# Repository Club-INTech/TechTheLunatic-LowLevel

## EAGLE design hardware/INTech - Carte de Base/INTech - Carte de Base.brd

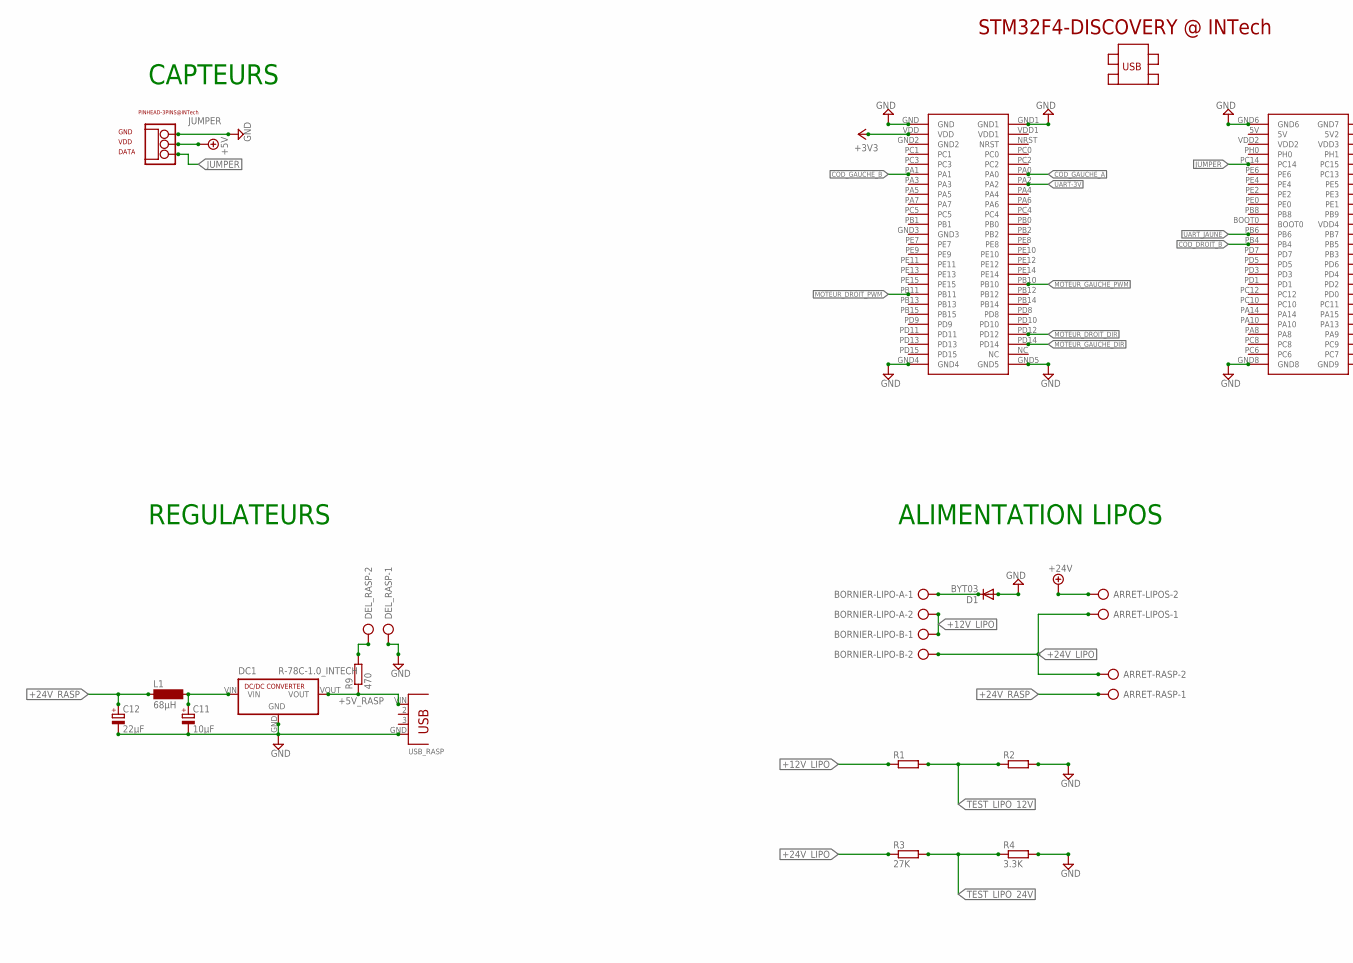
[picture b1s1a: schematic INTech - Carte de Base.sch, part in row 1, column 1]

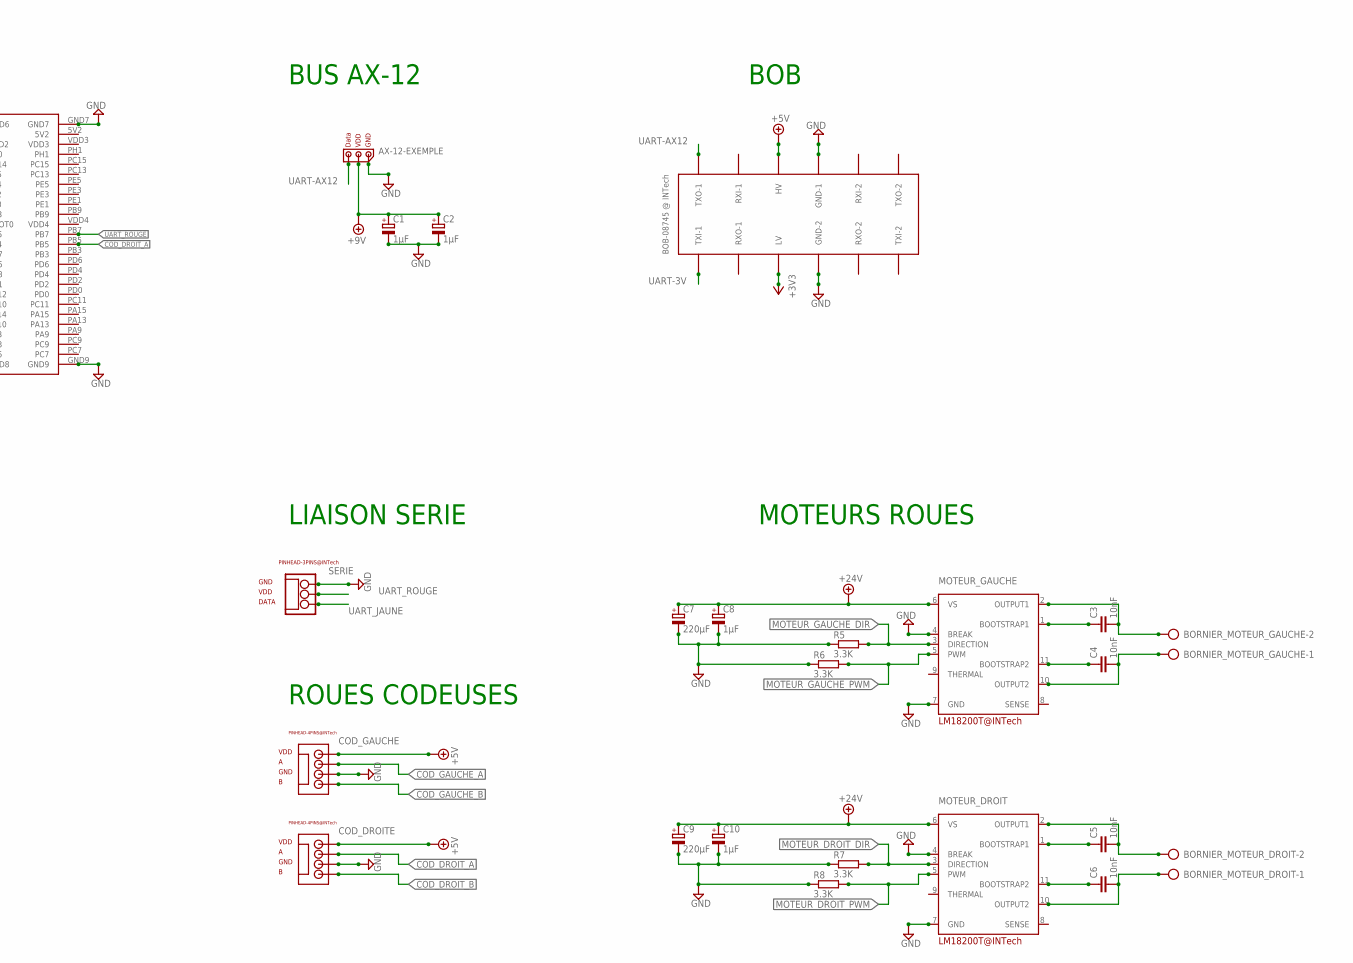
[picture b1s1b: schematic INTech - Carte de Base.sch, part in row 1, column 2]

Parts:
ARRET-LIPOS: AK300/2
ARRET-RASP: AK300/2
AX-12-EXEMPLE: AX-12_CF_INTECH
BORNIER-LIPO-A: AK300/2
BORNIER-LIPO-B: AK300/2
BORNIER_MOTEUR_DROIT: AK300/2
BORNIER_MOTEUR_GAUCHE: AK300/2
C1, C2: 1µF; E2,5-6E
C3, C4, C5, C6: 10nF; C050-025X075
C7, C9: 220µF; E3,5-8
C8, C10: 1µF; E3,5-8
C11: 10µF; E2,5-6
C12: 22µF; E2,5-6
COD_DROITE: PINHEAD-4_CF_INTECH
COD_GAUCHE: PINHEAD-4_CF_INTECH
D1: BYT03; DO27-15
DC1: R-78C-1.0_INTECH; SIP3_INTECH
DEL_RASP: AK300/2
JUMPER: PINHEAD_CF_INTECH
L1: 68µH; SD12K100
MOTEUR_DROIT: LM18200T_CF_INTECH
MOTEUR_GAUCHE: LM18200T_CF_INTECH
R1, R2: R-EU_0207/10; 0207/10
R3: 27K; 0207/10
R4, R5, R6, R7, R8: 3.3K; 0207/10
R9: 470; 0204/7
SERIE: PINHEAD_CF_INTECH
U$1: STM32F4-DISCOVERY
U$2: BOB-08745
USB_RASP: USB_87520; USB

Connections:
+3V3: U$1.VDD, U$2.LV
+5V: COD_DROITE.VDD, COD_GAUCHE.VDD, JUMPER.VDD, U$2.HV
+5V_RASP: DC1.VOUT, R9.1, USB_RASP.VIN
+9V: AX-12-EXEMPLE.VDD, C1.+, C2.+
+12V_LIPO: BORNIER-LIPO-A.2, BORNIER-LIPO-B.1, R1.1
+24V: ARRET-LIPOS.2, C7.+, C8.+, C9.+, C10.+, MOTEUR_DROIT.6 (VS), MOTEUR_GAUCHE.6 (VS)
+24V_LIPO: ARRET-LIPOS.1, ARRET-RASP.2, BORNIER-LIPO-B.2, R3.1
+24V_RASP: ARRET-RASP.1, C12.+, L1.1
COD_DROIT_A: COD_DROITE.A, U$1.PB5
COD_DROIT_B: COD_DROITE.B, U$1.PB4
COD_GAUCHE_A: COD_GAUCHE.A, U$1.PA0
COD_GAUCHE_B: COD_GAUCHE.B, U$1.PA1
GND: AX-12-EXEMPLE.GND, C1.-, C2.-, C7.-, C8.-, C9.-, C10.-, C11.-, C12.-, COD_DROITE.GND, COD_GAUCHE.GND, D1.A, DC1.GND, DEL_RASP.1, JUMPER.GND, MOTEUR_DROIT.4 (BREAK), MOTEUR_DROIT.7 (GND), MOTEUR_GAUCHE.4 (BREAK), MOTEUR_GAUCHE.7 (GND), R2.2, R4.2, R5.1, R6.1, R7.1, R8.1, SERIE.GND, U$1.GND, U$1.GND1, U$1.GND4, U$1.GND5, U$1.GND6, U$1.GND7, U$1.GND8, U$1.GND9, U$2.GND-1, U$2.GND-2, USB_RASP.GND
JUMPER: JUMPER.DATA, U$1.PC14
MOTEUR_DROIT_DIR: MOTEUR_DROIT.3 (DIRECTION), R7.2, U$1.PD12
MOTEUR_DROIT_PWM: MOTEUR_DROIT.5 (PWM), R8.2, U$1.PB11
MOTEUR_GAUCHE_DIR: MOTEUR_GAUCHE.3 (DIRECTION), R5.2, U$1.PD14
MOTEUR_GAUCHE_PWM: MOTEUR_GAUCHE.5 (PWM), R6.2, U$1.PB10
unnamed: BORNIER-LIPO-A.1, D1.C
unnamed: C4.1, MOTEUR_GAUCHE.11 (BOOTSTRAP2)
unnamed: C3.1, MOTEUR_GAUCHE.1 (BOOTSTRAP1)
unnamed: C5.1, MOTEUR_DROIT.1 (BOOTSTRAP1)
unnamed: C6.1, MOTEUR_DROIT.11 (BOOTSTRAP2)
unnamed: C11.+, DC1.VIN, L1.2
unnamed: DEL_RASP.2, R9.2
unnamed: BORNIER_MOTEUR_GAUCHE.2, C3.2, MOTEUR_GAUCHE.2 (OUTPUT1)
unnamed: BORNIER_MOTEUR_GAUCHE.1, C4.2, MOTEUR_GAUCHE.10 (OUTPUT2)
unnamed: BORNIER_MOTEUR_DROIT.2, C5.2, MOTEUR_DROIT.2 (OUTPUT1)
unnamed: BORNIER_MOTEUR_DROIT.1, C6.2, MOTEUR_DROIT.10 (OUTPUT2)
TEST_LIPO_12V: R1.2, R2.1
TEST_LIPO_24V: R3.2, R4.1
UART-3V: U$1.PA2, U$2.TXI-1
UART-AX12: AX-12-EXEMPLE.DATA, U$2.TXO-1
UART_JAUNE: SERIE.DATA, U$1.PB6
UART_ROUGE: SERIE.VDD, U$1.PB7

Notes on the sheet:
BUS AX-12
BOB
ALIMENTATION LIPOS
LIAISON SERIE
MOTEURS ROUES
ROUES CODEUSES
CAPTEURS
REGULATEURS

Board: 2 copper layers, 41 parts (0 on the bottom side), 35 nets, no tracks yet.

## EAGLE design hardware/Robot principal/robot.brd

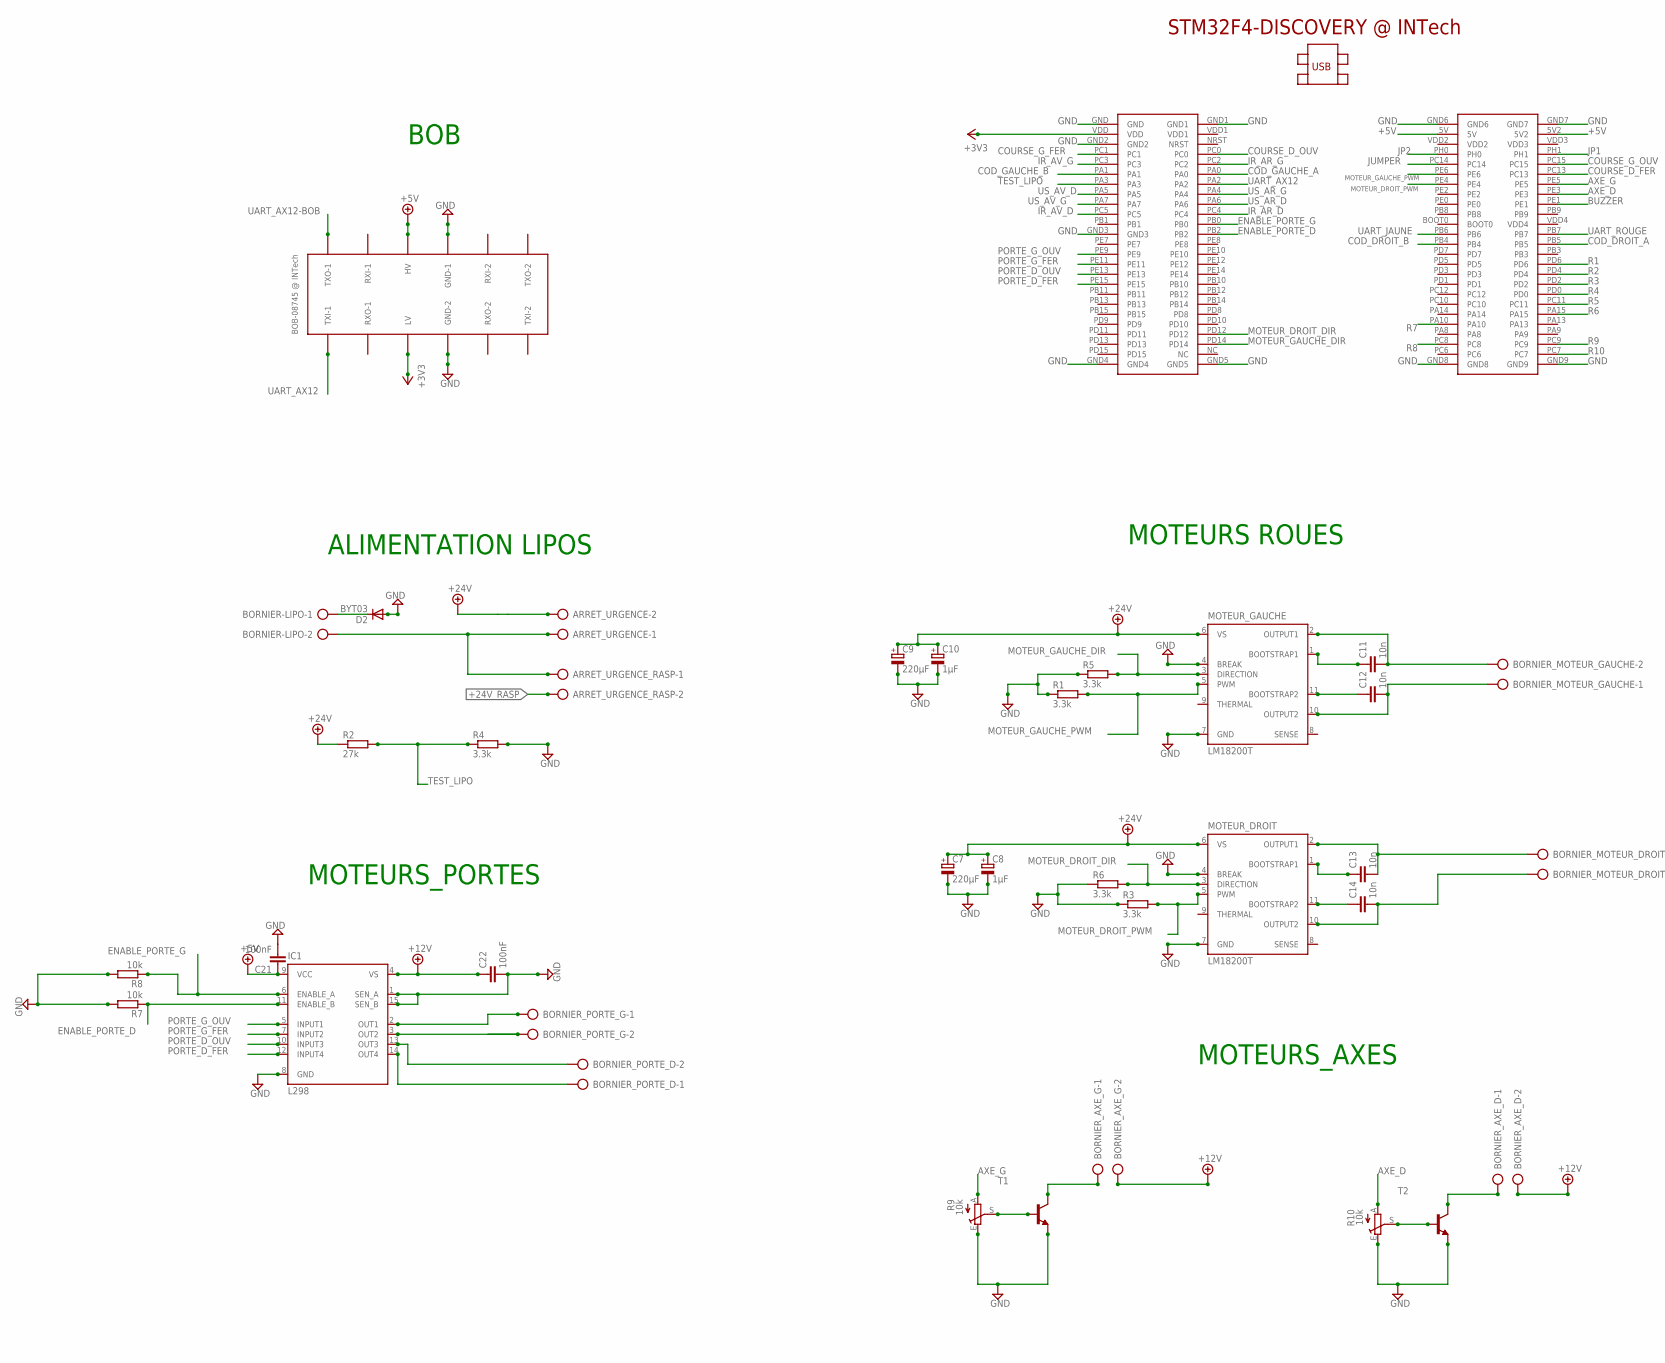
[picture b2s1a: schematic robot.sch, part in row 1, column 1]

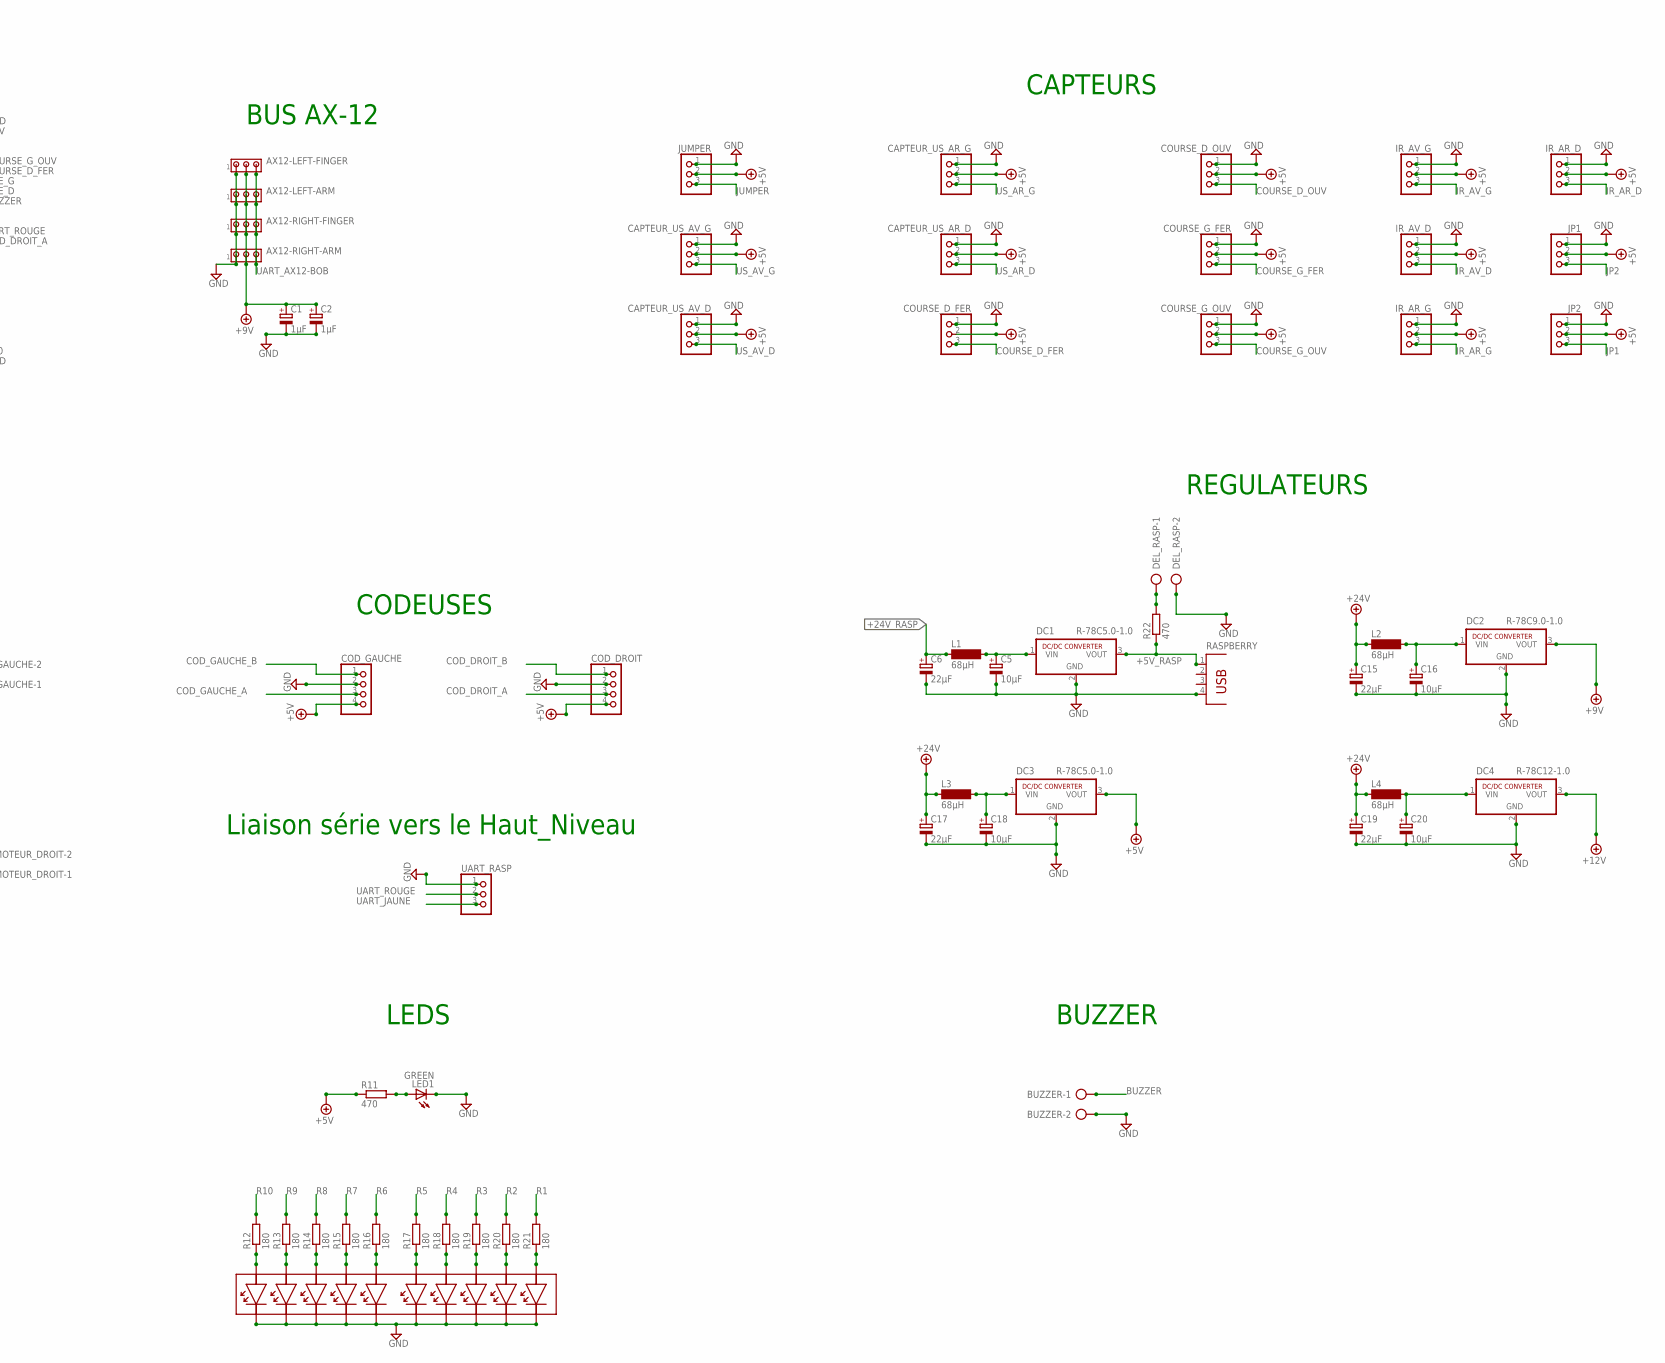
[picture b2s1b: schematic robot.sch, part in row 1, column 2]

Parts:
ARRET_URGENCE: AK300/2
ARRET_URGENCE_RASP: AK300/2
AX12-LEFT-ARM, AX12-LEFT-FINGER, AX12-RIGHT-ARM, AX12-RIGHT-FINGER: MTA03-100; 10X03MTA
BOB-08745: BOB-08745
BORNIER-LIPO: AK300/2
BORNIER_AXE_D: AK300/2
BORNIER_AXE_G: AK300/2
BORNIER_MOTEUR_DROIT: AK300/2
BORNIER_MOTEUR_GAUCHE: AK300/2
BORNIER_PORTE_D: AK300/2
BORNIER_PORTE_G: AK300/2
BUZZER: AK300/2
C1, C2: 1µF; E2,5-6E
C5, C16, C18, C20: 10µF; E2,5-6E
C6, C15, C17, C19: 22µF; E2,5-6E
C7, C9: 220µF; E3,5-8
C8, C10: 1µF; E3,5-8
C11, C12, C13, C14: 10n; C050-025X075
C21, C22: 100nF; C050-024X044
CAPTEUR_US_AR_D: PINHD-1X3; 1X03
CAPTEUR_US_AR_G: PINHD-1X3; 1X03
CAPTEUR_US_AV_D: PINHD-1X3; 1X03
CAPTEUR_US_AV_G: PINHD-1X3; 1X03
COD_DROIT: PINHD-1X4; 1X04
COD_GAUCHE: PINHD-1X4; 1X04
COURSE_D_FER: PINHD-1X3; 1X03
COURSE_D_OUV: PINHD-1X3; 1X03
COURSE_G_FER: PINHD-1X3; 1X03
COURSE_G_OUV: PINHD-1X3; 1X03
D2: BYT03; DO27-15
DC1, DC3: R-78C5.0-1.0; SIP3
DC2: R-78C9.0-1.0; SIP3
DC4: R-78C12-1.0; SIP3
DEL_RASP: AK300/2
IC1: L298; MULTIWATT-15
IR_AR_D: PINHD-1X3; 1X03
IR_AR_G: PINHD-1X3; 1X03
IR_AV_D: PINHD-1X3; 1X03
IR_AV_G: PINHD-1X3; 1X03
JP1, JP2: PINHD-1X3; 1X03
JUMPER: PINHD-1X3; 1X03
L1, L2, L3, L4: 68µH; SD12K100
LED1: GREEN; LED5MM
MOTEUR_DROIT: LM18200T; TO-220-11
MOTEUR_GAUCHE: LM18200T; TO-220-11
R1, R3: 3.3k; 0207/7
R2: 27k; 0207/10
R4, R5, R6: 3.3k; 0207/10
R7, R8: 10k; 0207/10
R9, R10: 10k; CA9H
R11: 470; 0207/2V
R12, R13, R14, R15, R16, R17, R18, R19, R20, R21: 180; 0207/2V
R22: 470; 0204/7
RASPBERRY: PN87520
T1, T2: 2N5400-NPN-TO92-CBE; TO92-CBE
U$1: STM32F4-DISCOVERY
U$2: DELS10RACK
UART_RASP: PINHD-1X3; 1X03

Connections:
+3V3: BOB-08745.LV, U$1.VDD
+5V: BOB-08745.HV, C21.1, CAPTEUR_US_AR_D.2, CAPTEUR_US_AR_G.2, CAPTEUR_US_AV_D.2, CAPTEUR_US_AV_G.2, COD_DROIT.4, COD_GAUCHE.4, COURSE_D_FER.2, COURSE_D_OUV.2, COURSE_G_FER.2, COURSE_G_OUV.2, DC3.3 (VOUT), IC1.9 (VCC), IR_AR_D.2, IR_AR_G.2, IR_AV_D.2, IR_AV_G.2, JP1.2, JP2.2, JUMPER.2, R11.1, U$1.5V, U$1.5V2
+5V_RASP: DC1.3 (VOUT), R22.1, RASPBERRY.1
+9V: AX12-LEFT-ARM.2, AX12-LEFT-FINGER.2, AX12-RIGHT-ARM.2, AX12-RIGHT-FINGER.2, C1.+, C2.+, DC2.3 (VOUT)
+12V: BORNIER_AXE_D.2, BORNIER_AXE_G.2, C22.1, DC4.3 (VOUT), IC1.4 (VS)
+24V: ARRET_URGENCE.2, C7.+, C8.+, C9.+, C10.+, C15.+, C17.+, C19.+, L2.1, L3.1, L4.1, MOTEUR_DROIT.6 (VS), MOTEUR_GAUCHE.6 (VS), R2.1
+24V_LIPO: ARRET_URGENCE.1, ARRET_URGENCE_RASP.1, BORNIER-LIPO.2
+24V_RASP: ARRET_URGENCE_RASP.2, C6.+, L1.1
AXE_D: R10.A, U$1.PE3
AXE_G: R9.A, U$1.PE5
BUZZER: BUZZER.1, U$1.PE1
COD_DROIT_A: COD_DROIT.3, U$1.PB5
COD_DROIT_B: COD_DROIT.1, U$1.PB4
COD_GAUCHE_A: COD_GAUCHE.3, U$1.PA0
COD_GAUCHE_B: COD_GAUCHE.1, U$1.PA1
COURSE_D_FER: COURSE_D_FER.3, U$1.PC13
COURSE_D_OUV: COURSE_D_OUV.3, U$1.PC0
COURSE_G_FER: COURSE_G_FER.3, U$1.PC1
COURSE_G_OUV: COURSE_G_OUV.3, U$1.PC15
ENABLE_PORTE_D: IC1.11 (ENABLE_B), R7.1, U$1.PB2
ENABLE_PORTE_G: IC1.6 (ENABLE_A), R8.1, U$1.PB0
GND: AX12-LEFT-ARM.1, AX12-LEFT-FINGER.1, AX12-RIGHT-ARM.1, AX12-RIGHT-FINGER.1, BOB-08745.GND-1, BOB-08745.GND-2, BUZZER.2, C1.-, C2.-, C5.-, C6.-, C7.-, C8.-, C9.-, C10.-, C15.-, C16.-, C17.-, C18.-, C19.-, C20.-, C21.2, C22.2, CAPTEUR_US_AR_D.1, CAPTEUR_US_AR_G.1, CAPTEUR_US_AV_D.1, CAPTEUR_US_AV_G.1, COD_DROIT.2, COD_GAUCHE.2, COURSE_D_FER.1, COURSE_D_OUV.1, COURSE_G_FER.1, COURSE_G_OUV.1, D2.A, DC1.2 (GND), DC2.2 (GND), DC3.2 (GND), DC4.2 (GND), DEL_RASP.2, IC1.1 (SEN_A), IC1.8 (GND), IC1.15 (SEN_B), IR_AR_D.1, IR_AR_G.1, IR_AV_D.1, IR_AV_G.1, JP1.1, JP2.1, JUMPER.1, LED1.K (C), MOTEUR_DROIT.4 (BREAK), MOTEUR_DROIT.7 (GND), MOTEUR_GAUCHE.4 (BREAK), MOTEUR_GAUCHE.7 (GND), R1.1, R3.1, R4.2, R5.1, R6.1, R7.2, R8.2, R9.E, R10.E, RASPBERRY.4, T1.E, T2.E, U$1.GND, U$1.GND1, U$1.GND2, U$1.GND3, U$1.GND4, U$1.GND5, U$1.GND6, U$1.GND7, U$1.GND8, U$1.GND9, U$2.11, U$2.12, U$2.13, U$2.14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
IR_AR_D: IR_AR_D.3, U$1.PC4
IR_AR_G: IR_AR_G.3, U$1.PC2
IR_AV_D: IR_AV_D.3, U$1.PC5
IR_AV_G: IR_AV_G.3, U$1.PC3
JP1: JP2.3, U$1.PH1
JP2: JP1.3, U$1.PH0
JUMPER: JUMPER.3, U$1.PC14
MOTEUR_DROIT_DIR: MOTEUR_DROIT.3 (DIRECTION), R6.2, U$1.PD12
MOTEUR_DROIT_PWM: MOTEUR_DROIT.5 (PWM), R3.2, U$1.PE4
MOTEUR_GAUCHE_DIR: MOTEUR_GAUCHE.3 (DIRECTION), R5.2, U$1.PD14
MOTEUR_GAUCHE_PWM: MOTEUR_GAUCHE.5 (PWM), R1.2, U$1.PE6
unnamed: R10.S, T2.B
unnamed: R9.S, T1.B
unnamed: DEL_RASP.1, R22.2
unnamed: BORNIER-LIPO.1, D2.C
unnamed: BORNIER_AXE_G.1, T1.C
unnamed: LED1.A, R11.2
unnamed: BORNIER_PORTE_D.1, IC1.14 (OUT4)
unnamed: C14.1, MOTEUR_DROIT.11 (BOOTSTRAP2)
unnamed: BORNIER_MOTEUR_GAUCHE.1, C12.2, MOTEUR_GAUCHE.10 (OUTPUT2)
unnamed: C11.1, MOTEUR_GAUCHE.1 (BOOTSTRAP1)
unnamed: BORNIER_MOTEUR_DROIT.2, C13.2, MOTEUR_DROIT.2 (OUTPUT1)
unnamed: BORNIER_MOTEUR_DROIT.1, C14.2, MOTEUR_DROIT.10 (OUTPUT2)
unnamed: C20.+, DC4.1 (VIN), L4.2
unnamed: C13.1, MOTEUR_DROIT.1 (BOOTSTRAP1)
unnamed: C5.+, DC1.1 (VIN), L1.2
unnamed: BORNIER_MOTEUR_GAUCHE.2, C11.2, MOTEUR_GAUCHE.2 (OUTPUT1)
unnamed: C18.+, DC3.1 (VIN), L3.2
unnamed: C12.1, MOTEUR_GAUCHE.11 (BOOTSTRAP2)
unnamed: C16.+, DC2.1 (VIN), L2.2
unnamed: R12.1, U$2.10
unnamed: R13.1, U$2.9
unnamed: BORNIER_AXE_D.1, T2.C
unnamed: R14.1, U$2.8
unnamed: BORNIER_PORTE_G.1, IC1.2 (OUT1)
unnamed: R15.1, U$2.7
unnamed: BORNIER_PORTE_G.2, IC1.3 (OUT2)
unnamed: BORNIER_PORTE_D.2, IC1.13 (OUT3)
unnamed: R16.1, U$2.6
unnamed: R17.1, U$2.5
unnamed: R18.1, U$2.4
unnamed: R19.1, U$2.3
unnamed: R20.1, U$2.2
unnamed: R21.1, U$2.1
PORTE_D_FER: IC1.12 (INPUT4), U$1.PE15
PORTE_D_OUV: IC1.10 (INPUT3), U$1.PE13
PORTE_G_FER: IC1.7 (INPUT2), U$1.PE11
PORTE_G_OUV: IC1.5 (INPUT1), U$1.PE9
R1: R21.2, U$1.PD6
R2: R20.2, U$1.PD4
R3: R19.2, U$1.PD2
R4: R18.2, U$1.PD0
R5: R17.2, U$1.PC11
R6: R16.2, U$1.PA15
R7: R15.2, U$1.PA10
R8: R14.2, U$1.PC8
R9: R13.2, U$1.PC9
R10: R12.2, U$1.PC7
TEST_LIPO: R2.2, R4.1, U$1.PA3
UART_AX12: BOB-08745.TXI-1, U$1.PA2
UART_AX12-BOB: AX12-LEFT-ARM.3, AX12-LEFT-FINGER.3, AX12-RIGHT-ARM.3, AX12-RIGHT-FINGER.3, BOB-08745.TXO-1
UART_JAUNE: U$1.PB6, UART_RASP.3
UART_ROUGE: U$1.PB7, UART_RASP.2
US_AR_D: CAPTEUR_US_AR_D.3, U$1.PA6
US_AR_G: CAPTEUR_US_AR_G.3, U$1.PA4
US_AV_D: CAPTEUR_US_AV_D.3, U$1.PA5
US_AV_G: CAPTEUR_US_AV_G.3, U$1.PA7

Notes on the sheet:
BUS AX-12
CAPTEURS
CODEUSES
Liaison série vers le Haut_Niveau
MOTEURS ROUES
REGULATEURS
BOB
ALIMENTATION LIPOS
MOTEURS_PORTES
MOTEURS_AXES
LEDS
BUZZER

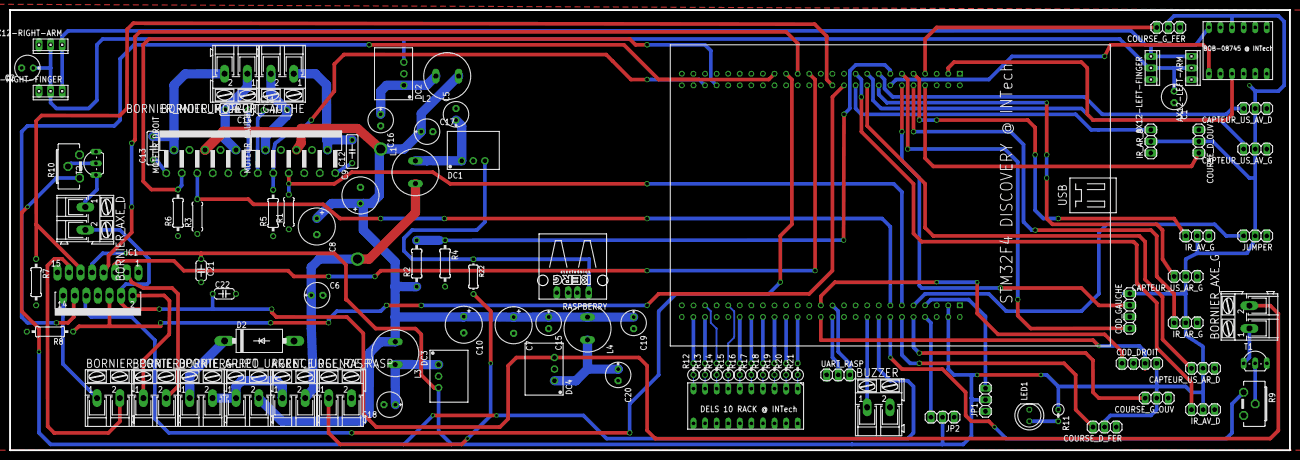
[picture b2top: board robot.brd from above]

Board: 2 copper layers, 280.7 x 96.5 mm, 94 parts (0 on the bottom side), 89 nets.

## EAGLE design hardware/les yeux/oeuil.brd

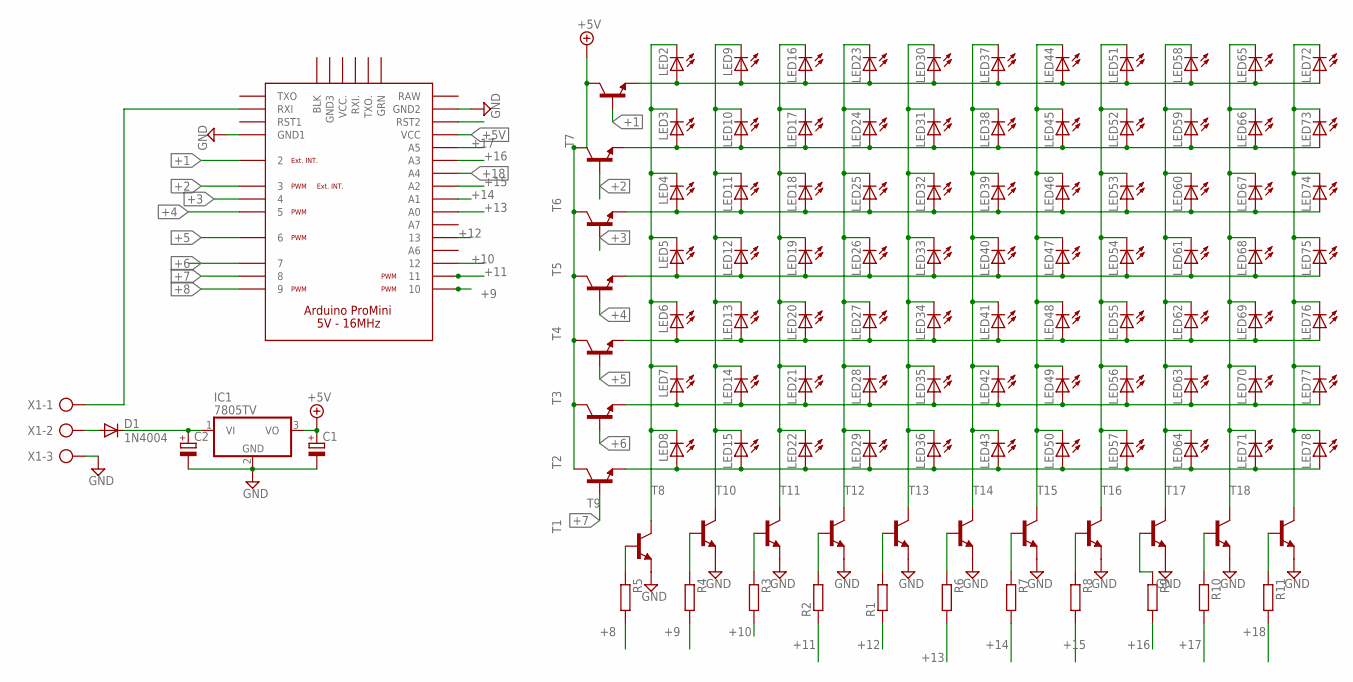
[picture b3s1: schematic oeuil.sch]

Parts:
C1, C2: CPOL-EUE2,5-6E; E2,5-6E
D1: 1N4004; DO41-10
IC1: 7805TV; TO220V
LED2, LED3, LED4, LED5, LED6, LED7, LED8, LED9, LED10, LED11, LED12, LED13, LED14, LED15, LED16, LED17, LED18, LED19, LED20, LED21, LED22, LED23, LED24, LED25, LED26, LED27, LED28, LED29, LED30, LED31, LED32, LED33, LED34, LED35, LED36, LED37, LED38, LED39, LED40, LED41, LED42, LED43, LED44, LED45, LED46, LED47, LED48, LED49, LED50, LED51, LED52, LED53, LED54, LED55, LED56, LED57, LED58, LED59, LED60, LED61, LED62, LED63, LED64, LED65, LED66, LED67, LED68, LED69, LED70, LED71, LED72, LED73, LED74, LED75, LED76, LED77, LED78: LED3MM
R1, R2, R3, R4, R5, R6, R7, R8, R9, R10, R11: R-EU_0207/2V; 0207/2V
T1, T2, T3, T4, T5, T6, T7, T8, T9, T10, T11, T12, T13, T14, T15, T16, T17, T18: 2N4124-NPN-TO92-CBE; TO92-CBE
U$1: ARDUINO_PRO_MINI
X1: AK300/3

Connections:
+1: T7.B, U$1.2
+2: T6.B, U$1.3
+3: T5.B, U$1.4
+4: T4.B, U$1.5
+5: T3.B, U$1.6
+5V: C1.+, IC1.3 (VO), T1.C, T2.C, T3.C, T4.C, T5.C, T6.C, T7.C, U$1.VCC1 (VCC)
+6: T2.B, U$1.7
+7: T1.B, U$1.8
+8: R5.2, U$1.9
+9: R4.2, U$1.10
+10: R3.2, U$1.12
+11: R2.1, U$1.11
+12: R1.1, U$1.13
+13: R6.2, U$1.A0
+14: R7.2, U$1.A1
+15: R8.2, U$1.A2
+16: R9.2, U$1.A3
+17: R10.2, U$1.A5
+18: R11.2, U$1.A4
GND: C1.-, C2.-, IC1.2 (GND), T8.E, T9.E, T10.E, T11.E, T12.E, T13.E, T14.E, T15.E, T16.E, T17.E, T18.E, U$1.GND1, U$1.GND2, X1.3
unnamed: C2.+, D1.C, IC1.1 (VI)
unnamed: LED9.K (C), LED10.K (C), LED11.K (C), LED12.K (C), LED13.K (C), LED14.K (C), LED15.K (C), T8.C
unnamed: LED16.K (C), LED17.K (C), LED18.K (C), LED19.K (C), LED20.K (C), LED21.K (C), LED22.K (C), T10.C
unnamed: LED51.K (C), LED52.K (C), LED53.K (C), LED54.K (C), LED55.K (C), LED56.K (C), LED57.K (C), T15.C
unnamed: LED23.K (C), LED24.K (C), LED25.K (C), LED26.K (C), LED27.K (C), LED28.K (C), LED29.K (C), T11.C
unnamed: LED30.K (C), LED31.K (C), LED32.K (C), LED33.K (C), LED34.K (C), LED35.K (C), LED36.K (C), T12.C
unnamed: LED37.K (C), LED38.K (C), LED39.K (C), LED40.K (C), LED41.K (C), LED42.K (C), LED43.K (C), T13.C
unnamed: LED44.K (C), LED45.K (C), LED46.K (C), LED47.K (C), LED48.K (C), LED49.K (C), LED50.K (C), T14.C
unnamed: LED58.K (C), LED59.K (C), LED60.K (C), LED61.K (C), LED62.K (C), LED63.K (C), LED64.K (C), T16.C
unnamed: LED65.K (C), LED66.K (C), LED67.K (C), LED68.K (C), LED69.K (C), LED70.K (C), LED71.K (C), T17.C
unnamed: LED72.K (C), LED73.K (C), LED74.K (C), LED75.K (C), LED76.K (C), LED77.K (C), LED78.K (C), T18.C
unnamed: LED8.A, LED15.A, LED22.A, LED29.A, LED36.A, LED43.A, LED50.A, LED57.A, LED64.A, LED71.A, LED78.A, T1.E
unnamed: R5.1, T9.B
unnamed: R4.1, T8.B
unnamed: R3.1, T10.B
unnamed: R2.2, T11.B
unnamed: R1.2, T12.B
unnamed: R6.1, T13.B
unnamed: R7.1, T14.B
unnamed: R8.1, T15.B
unnamed: R9.1, T16.B
unnamed: R10.1, T17.B
unnamed: R11.1, T18.B
unnamed: LED2.A, LED9.A, LED16.A, LED23.A, LED30.A, LED37.A, LED44.A, LED51.A, LED58.A, LED65.A, LED72.A, T7.E
unnamed: D1.A, X1.2
unnamed: U$1.RXI1 (RXI), X1.1
unnamed: LED6.A, LED13.A, LED20.A, LED27.A, LED34.A, LED41.A, LED48.A, LED55.A, LED62.A, LED69.A, LED76.A, T3.E
unnamed: LED7.A, LED14.A, LED21.A, LED28.A, LED35.A, LED42.A, LED49.A, LED56.A, LED63.A, LED70.A, LED77.A, T2.E
unnamed: LED5.A, LED12.A, LED19.A, LED26.A, LED33.A, LED40.A, LED47.A, LED54.A, LED61.A, LED68.A, LED75.A, T4.E
unnamed: LED4.A, LED11.A, LED18.A, LED25.A, LED32.A, LED39.A, LED46.A, LED53.A, LED60.A, LED67.A, LED74.A, T5.E
unnamed: LED3.A, LED10.A, LED17.A, LED24.A, LED31.A, LED38.A, LED45.A, LED52.A, LED59.A, LED66.A, LED73.A, T6.E
unnamed: LED2.K (C), LED3.K (C), LED4.K (C), LED5.K (C), LED6.K (C), LED7.K (C), LED8.K (C), T9.C

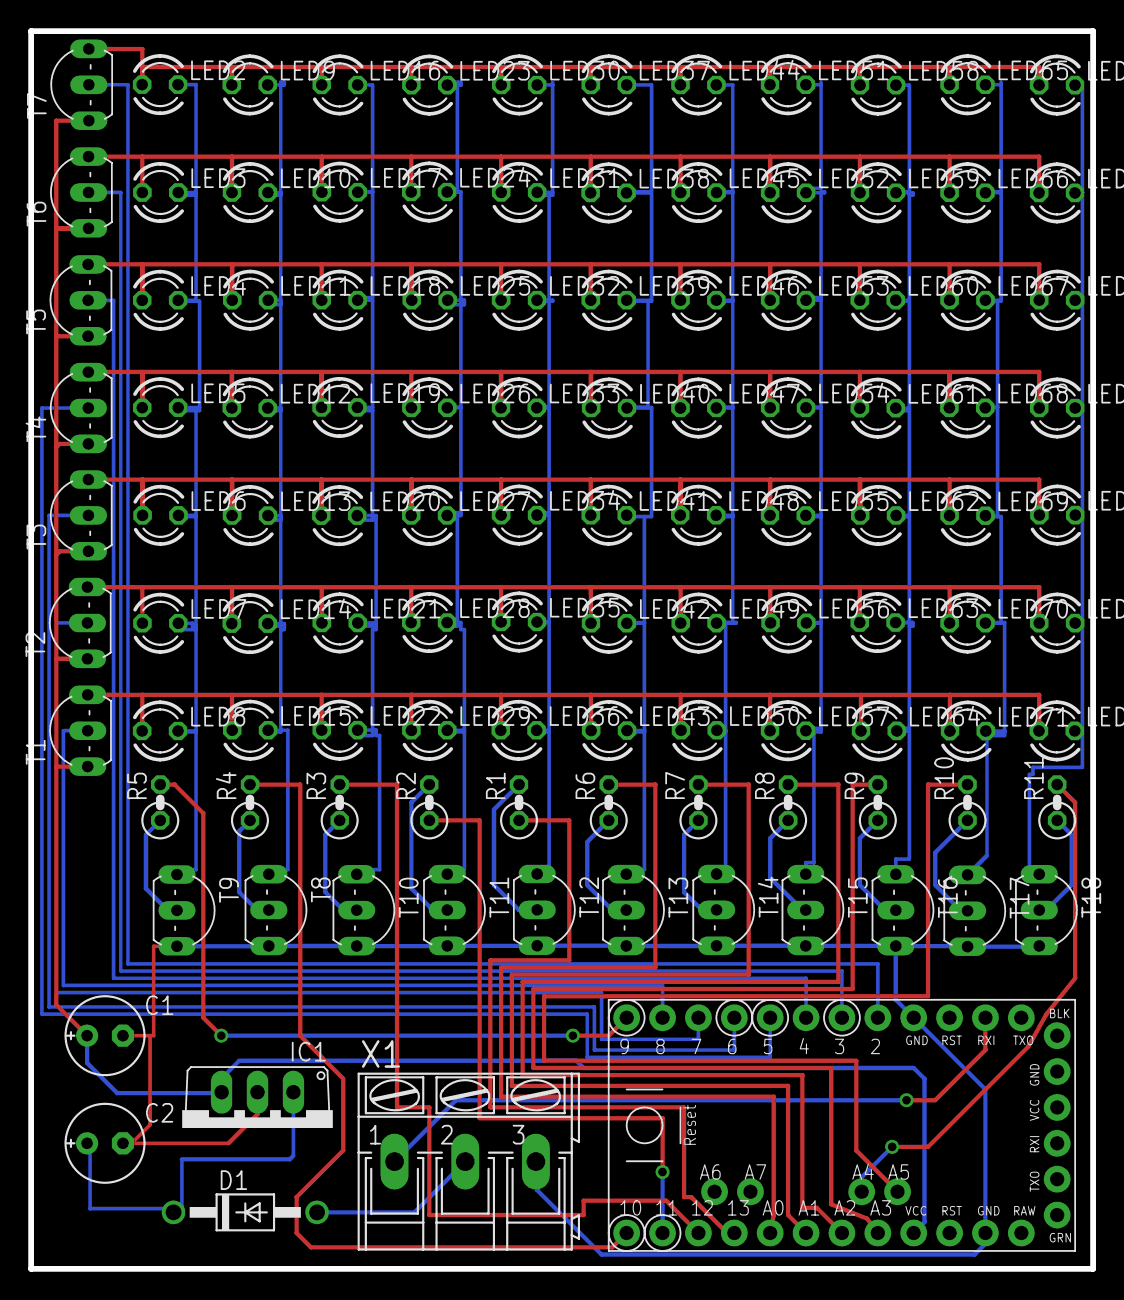
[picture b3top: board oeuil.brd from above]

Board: 2 copper layers, 75.2 x 87.6 mm, 112 parts (0 on the bottom side), 52 nets.

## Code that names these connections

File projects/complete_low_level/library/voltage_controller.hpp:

#include "stm32f4xx.h"
#include "safe_enum.hpp"
#include "utils.h"
#include "stm32f4xx_gpio.h"
#include "stm32f4xx_tim.h"
#include "stm32f4xx_rcc.h"
#include "stm32f4xx_adc.h"

/**
 * Permet de mesurer la tension de la LiPO et l'affiche sur un indicateur � 10 LEDs
 *
 * LEDS:
 * 1: PC7
 * 2: PC8
 * 3: PC9
 * 4: PE0
 * 5: PA15
 * 6: PC11
 * 7: PD0
 * 8: PD2
 * 9: PD4
 * 10: PD6
 * @author discord & sa maman
 */
class Voltage_controller : public Singleton<Voltage_controller>
{
public:
	Voltage_controller()
	{
		counter = 0;
		blink = false;
		minimal_voltage = 4086;
		usb_voltage = 600;
		voltage_echelon = 80;

		RCC_AHB1PeriphClockCmd(RCC_AHB1Periph_GPIOB, ENABLE);
		RCC_AHB1PeriphClockCmd(RCC_AHB1Periph_GPIOD, ENABLE);
		RCC_AHB1PeriphClockCmd(RCC_AHB1Periph_GPIOC, ENABLE);
		RCC_AHB1PeriphClockCmd(RCC_AHB1Periph_GPIOA, ENABLE);
		RCC_AHB1PeriphClockCmd(RCC_AHB1Periph_GPIOE, ENABLE);

		GPIO_InitTypeDef GPIO_InitStruct;
		GPIO_StructInit(&GPIO_InitStruct); //Remplit avec les valeurs par d�faut

		GPIO_InitStruct.GPIO_Pin = GPIO_Pin_6;
		GPIO_InitStruct.GPIO_Mode = GPIO_Mode_OUT;
		GPIO_InitStruct.GPIO_Speed = GPIO_Speed_100MHz;
		GPIO_Init(GPIOD, &GPIO_InitStruct);

		GPIO_StructInit(&GPIO_InitStruct); //Remplit avec les valeurs par d�faut

		GPIO_InitStruct.GPIO_Pin = GPIO_Pin_4;
		GPIO_InitStruct.GPIO_Mode = GPIO_Mode_OUT;
		GPIO_InitStruct.GPIO_Speed = GPIO_Speed_100MHz;
		GPIO_Init(GPIOD, &GPIO_InitStruct);

		GPIO_StructInit(&GPIO_InitStruct); //Remplit avec les valeurs par d�faut

		GPIO_InitStruct.GPIO_Pin = GPIO_Pin_2;
		GPIO_InitStruct.GPIO_Mode = GPIO_Mode_OUT;
		GPIO_InitStruct.GPIO_Speed = GPIO_Speed_100MHz;
		GPIO_Init(GPIOD, &GPIO_InitStruct);

		GPIO_StructInit(&GPIO_InitStruct); //Remplit avec les valeurs par d�faut

		GPIO_InitStruct.GPIO_Pin = GPIO_Pin_0;
		GPIO_InitStruct.GPIO_Mode = GPIO_Mode_OUT;
		GPIO_InitStruct.GPIO_Speed = GPIO_Speed_100MHz;
		GPIO_Init(GPIOD, &GPIO_InitStruct);

		GPIO_StructInit(&GPIO_InitStruct); //Remplit avec les valeurs par d�faut

		GPIO_InitStruct.GPIO_Pin = GPIO_Pin_11;
		GPIO_InitStruct.GPIO_Mode = GPIO_Mode_OUT;
		GPIO_InitStruct.GPIO_Speed = GPIO_Speed_100MHz;
		GPIO_Init(GPIOC, &GPIO_InitStruct);

		GPIO_StructInit(&GPIO_InitStruct); //Remplit avec les valeurs par d�faut

		GPIO_InitStruct.GPIO_Pin = GPIO_Pin_15;
		GPIO_InitStruct.GPIO_Mode = GPIO_Mode_OUT;
		GPIO_InitStruct.GPIO_Speed = GPIO_Speed_100MHz;
		GPIO_Init(GPIOA, &GPIO_InitStruct);

		GPIO_StructInit(&GPIO_InitStruct); //Remplit avec les valeurs par d�faut

		GPIO_InitStruct.GPIO_Pin = GPIO_Pin_0;
		GPIO_InitStruct.GPIO_Mode = GPIO_Mode_OUT;
		GPIO_InitStruct.GPIO_Speed = GPIO_Speed_100MHz;
		GPIO_Init(GPIOE, &GPIO_InitStruct);

		GPIO_StructInit(&GPIO_InitStruct); //Remplit avec les valeurs par d�faut

		GPIO_InitStruct.GPIO_Pin = GPIO_Pin_9;
		GPIO_InitStruct.GPIO_Mode = GPIO_Mode_OUT;
		GPIO_InitStruct.GPIO_Speed = GPIO_Speed_100MHz;
		GPIO_Init(GPIOC, &GPIO_InitStruct);

		GPIO_StructInit(&GPIO_InitStruct); //Remplit avec les valeurs par d�faut

		GPIO_InitStruct.GPIO_Pin = GPIO_Pin_8;
		GPIO_InitStruct.GPIO_Mode = GPIO_Mode_OUT;
		GPIO_InitStruct.GPIO_Speed = GPIO_Speed_100MHz;
		GPIO_Init(GPIOC, &GPIO_InitStruct);

		GPIO_StructInit(&GPIO_InitStruct); //Remplit avec les valeurs par d�faut

		GPIO_InitStruct.GPIO_Pin = GPIO_Pin_7;
		GPIO_InitStruct.GPIO_Mode = GPIO_Mode_OUT;
		GPIO_InitStruct.GPIO_Speed = GPIO_Speed_100MHz;
		GPIO_Init(GPIOC, &GPIO_InitStruct);


		GPIO_InitStruct.GPIO_Pin = GPIO_Pin_1; // BUZZER !!!
		GPIO_InitStruct.GPIO_Mode = GPIO_Mode_OUT;
		GPIO_InitStruct.GPIO_Speed = GPIO_Speed_100MHz;
		GPIO_Init(GPIOE, &GPIO_InitStruct);

		GPIO_StructInit(&GPIO_InitStruct);


		adc_configure();

	}

	void measure()
	{
		uint32_t ADCValue = 0;
		ADCValue = adc_convert();

		clear_leds();

		GPIO_ResetBits(GPIOE, GPIO_Pin_1);

		if(ADCValue >= voltage_echelon*9 + minimal_voltage )
		{
			GPIO_SetBits(GPIOD, GPIO_Pin_6);
		}
		if(ADCValue >= voltage_echelon*8 + minimal_voltage )
		{
			GPIO_SetBits(GPIOD, GPIO_Pin_4);
		}
		if(ADCValue >= voltage_echelon*7 + minimal_voltage )
		{
			GPIO_SetBits(GPIOD, GPIO_Pin_2);
		}
		if(ADCValue >= voltage_echelon*6 + minimal_voltage )
		{
			GPIO_SetBits(GPIOD, GPIO_Pin_0);
		}
		if(ADCValue >= voltage_echelon*5 + minimal_voltage )
		{
			GPIO_SetBits(GPIOC, GPIO_Pin_11);
		}
		if(ADCValue >= voltage_echelon*4 + minimal_voltage )
		{
			GPIO_SetBits(GPIOA, GPIO_Pin_15);
		}
		if(ADCValue >= voltage_echelon*3 + minimal_voltage )
		{
			GPIO_SetBits(GPIOE, GPIO_Pin_0);
		}
		if(ADCValue >= voltage_echelon*2 + minimal_voltage )
		{
			GPIO_SetBits(GPIOC, GPIO_Pin_9);
		}
		if(ADCValue >= voltage_echelon + minimal_voltage )
		{
			GPIO_SetBits(GPIOC, GPIO_Pin_8);
		}
		if(ADCValue >= minimal_voltage )
		{
			GPIO_SetBits(GPIOC, GPIO_Pin_7);
		}
		if(ADCValue < minimal_voltage)
		{

				if(ADCValue >= usb_voltage)
					GPIO_SetBits(GPIOE, GPIO_Pin_1);


				if(blink)
				{
					GPIO_SetBits(GPIOC, GPIO_Pin_7);
				}
				else
				{
					GPIO_ResetBits(GPIOC, GPIO_Pin_7);
				}
				blink = !blink;
			}
		}


	int test(){
		return(adc_convert());
	}

    void setMin(uint32_t newmin){
        this->minimal_voltage=newmin;
    }

    void setEchelon(uint32_t newechelon){
        this->voltage_echelon=newechelon;
    }

    uint32_t getEchelon(){
        return this->voltage_echelon;
    }
    uint32_t getMin(){
        return this->minimal_voltage;
    }

private:

	uint32_t voltage_echelon; //Cherches pas, y'a pas d'unit� SI.
	uint32_t minimal_voltage; //L� non plus.
	uint32_t usb_voltage;
	int counter; //L� t'es con si t'en cherches une...
	bool blink;


	void adc_configure(){
	 ADC_InitTypeDef ADC_init_structure; //Structure for adc confguration
	 GPIO_InitTypeDef GPIO_initStructre; //Structure for analog input pin
	 //Clock configuration
	 RCC_APB2PeriphClockCmd(RCC_APB2Periph_ADC3,ENABLE);//The ADC1 is connected the APB2 peripheral bus thus we will use its clock source
	 //RCC_AHB1PeriphClockCmd(RCC_AHB1ENR_GPIOCEN,ENABLE);//Clock for the ADC port!! Do not forget about this one ;)
	 //Analog pin configuration
	 GPIO_initStructre.GPIO_Pin = GPIO_Pin_3;//	The channel 10 is connected to PC0
	 GPIO_initStructre.GPIO_Mode = GPIO_Mode_AN; //The PC0 pin is configured in analog mode
	 GPIO_initStructre.GPIO_PuPd = GPIO_PuPd_NOPULL; //We don't need any pull up or pull down
	 GPIO_Init(GPIOA,&GPIO_initStructre);//Affecting the port with the initialization structure configuration
	 //ADC structure configuration
	 ADC_DeInit();
	 ADC_init_structure.ADC_DataAlign = ADC_DataAlign_Right;//data converted will be shifted to right
	 ADC_init_structure.ADC_Resolution = ADC_Resolution_12b;//Input voltage is converted into a 12bit number giving a maximum value of 4096
	 ADC_init_structure.ADC_ContinuousConvMode = ENABLE; //the conversion is continuous, the input data is converted more than once
	 ADC_init_structure.ADC_ExternalTrigConv = ADC_ExternalTrigConv_T1_CC1;// conversion is synchronous with TIM1 and CC1 (actually I'm not sure about this one :/)
	 ADC_init_structure.ADC_ExternalTrigConvEdge = ADC_ExternalTrigConvEdge_None;//no trigger for conversion
	 ADC_init_structure.ADC_NbrOfConversion = 1;//I think this one is clear :p
	 ADC_init_structure.ADC_ScanConvMode = DISABLE;//The scan is configured in one channel
	 ADC_Init(ADC3,&ADC_init_structure);//Initialize ADC with the previous configuration
	 //Enable ADC conversion
	 ADC_Cmd(ADC3,ENABLE);
	 //Select the channel to be read from
	 ADC_RegularChannelConfig(ADC3,ADC_Channel_3,1,ADC_SampleTime_144Cycles);
	}

	void clear_leds()
	{
		GPIO_ResetBits(GPIOD, GPIO_Pin_6);
		GPIO_ResetBits(GPIOD, GPIO_Pin_4);
		GPIO_ResetBits(GPIOD, GPIO_Pin_2);
		GPIO_ResetBits(GPIOD, GPIO_Pin_0);
		GPIO_ResetBits(GPIOC, GPIO_Pin_11);
		GPIO_ResetBits(GPIOA, GPIO_Pin_15);
		GPIO_ResetBits(GPIOA, GPIO_Pin_10);
		GPIO_ResetBits(GPIOC, GPIO_Pin_8);
		GPIO_ResetBits(GPIOC, GPIO_Pin_9);
		GPIO_ResetBits(GPIOC, GPIO_Pin_7);
	}


	int adc_convert(){
	 ADC_SoftwareStartConv(ADC3);//Start the conversion
	 while(!ADC_GetFlagStatus(ADC3, ADC_FLAG_EOC));//Processing the conversion
	 return ADC_GetConversionValue(ADC3); //Return the converted data
	}



};

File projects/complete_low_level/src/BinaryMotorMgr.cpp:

/*
 * BinaryMotor.cpp
 *
 * Classe de gestion des moteurs sans PWM
 *
 */

#include "BinaryMotorMgr.hpp"
#include "SensorMgr.h"


bool rightDoorOpening = false;
bool leftDoorOpening = false;
bool rightDoorClosing = false;
bool leftDoorClosing = false;

bool RightDoorBlocked = false;
bool LeftDoorBlocked = false;


uint32_t timeToStopDoor = 800;

uint32_t timeTooLong = 6000;

BinaryMotorMgr::BinaryMotorMgr() {



		/**
		 * Configuration des pins :
		 * Porte Gauche ouverture : PE9
		 * Porte gauche fermeture : PE11
		 * Porte Droite ouverture : PE13
		 * Porte droite fermeture : PE15
		 *
		 * Enable porte Gauche : PB0
		 * Enable porte Droite : PB2
		 *
		 * Axe gauche : PE5
		 * Axe droit : PE3
		 *
		 */

		GPIO_InitTypeDef GPIO_InitStruct;
		GPIO_StructInit(&GPIO_InitStruct); //Remplit avec les valeurs par défaut
		// Active l'horloge du port D
		RCC_AHB1PeriphClockCmd(RCC_AHB1Periph_GPIOE, ENABLE);
		RCC_AHB1PeriphClockCmd(RCC_AHB1Periph_GPIOB, ENABLE);


			GPIO_InitStruct.GPIO_Pin = GPIO_Pin_9;
			GPIO_InitStruct.GPIO_Mode = GPIO_Mode_OUT;
			GPIO_InitStruct.GPIO_Speed = GPIO_Speed_100MHz;
			GPIO_Init(GPIOE, &GPIO_InitStruct);

			GPIO_InitStruct.GPIO_Pin = GPIO_Pin_11;
			GPIO_InitStruct.GPIO_Mode = GPIO_Mode_OUT;
			GPIO_InitStruct.GPIO_Speed = GPIO_Speed_100MHz;
			GPIO_Init(GPIOE, &GPIO_InitStruct);


			GPIO_InitStruct.GPIO_Pin = GPIO_Pin_13;
			GPIO_InitStruct.GPIO_Mode = GPIO_Mode_OUT;
			GPIO_InitStruct.GPIO_Speed = GPIO_Speed_100MHz;
			GPIO_Init(GPIOE, &GPIO_InitStruct);

			GPIO_InitStruct.GPIO_Pin = GPIO_Pin_15;
			GPIO_InitStruct.GPIO_Mode = GPIO_Mode_OUT;
			GPIO_InitStruct.GPIO_Speed = GPIO_Speed_100MHz;
			GPIO_Init(GPIOE, &GPIO_InitStruct);

			GPIO_InitStruct.GPIO_Pin = GPIO_Pin_3;
			GPIO_InitStruct.GPIO_Mode = GPIO_Mode_OUT;
			GPIO_InitStruct.GPIO_Speed = GPIO_Speed_100MHz;
			GPIO_Init(GPIOE, &GPIO_InitStruct);

			GPIO_InitStruct.GPIO_Pin = GPIO_Pin_5;
			GPIO_InitStruct.GPIO_Mode = GPIO_Mode_OUT;
			GPIO_InitStruct.GPIO_Speed = GPIO_Speed_100MHz;
			GPIO_Init(GPIOE, &GPIO_InitStruct);

			GPIO_InitStruct.GPIO_Pin = GPIO_Pin_0;
			GPIO_InitStruct.GPIO_Mode = GPIO_Mode_OUT;
			GPIO_InitStruct.GPIO_Speed = GPIO_Speed_100MHz;
			GPIO_Init(GPIOB, &GPIO_InitStruct);

			GPIO_InitStruct.GPIO_Pin = GPIO_Pin_2;
			GPIO_InitStruct.GPIO_Mode = GPIO_Mode_OUT;
			GPIO_InitStruct.GPIO_Speed = GPIO_Speed_100MHz;
			GPIO_Init(GPIOB, &GPIO_InitStruct);

			GPIO_ResetBits(GPIOE, GPIO_Pin_9);
			GPIO_ResetBits(GPIOE, GPIO_Pin_11);
			GPIO_ResetBits(GPIOE, GPIO_Pin_13);
			GPIO_ResetBits(GPIOE, GPIO_Pin_15);

			GPIO_SetBits(GPIOB, GPIO_Pin_0);
			GPIO_SetBits(GPIOB, GPIO_Pin_2);

}

/*--- Axes rotatifs ---*/

void BinaryMotorMgr::runAxisLeft() {
	GPIO_SetBits(GPIOE, GPIO_Pin_5);
	}

void BinaryMotorMgr::runAxisRight() {
	GPIO_SetBits(GPIOE, GPIO_Pin_3);
	}

void BinaryMotorMgr::stopAxisLeft() {
	GPIO_ResetBits(GPIOE, GPIO_Pin_5);
	}

void BinaryMotorMgr::stopAxisRight() {
	GPIO_ResetBits(GPIOE, GPIO_Pin_3);
	}


/*--- Mouvement des portes ---*/

void BinaryMotorMgr::runForwardLeft() {

	GPIO_SetBits(GPIOE, GPIO_Pin_9);
	GPIO_ResetBits(GPIOE, GPIO_Pin_11);

}

void BinaryMotorMgr::runBackwardLeft() {

	GPIO_SetBits(GPIOE, GPIO_Pin_11);
	GPIO_ResetBits(GPIOE, GPIO_Pin_9);
}

void BinaryMotorMgr::runForwardRight() {

	GPIO_ResetBits(GPIOE, GPIO_Pin_15);
	GPIO_SetBits(GPIOE, GPIO_Pin_13);
}

void BinaryMotorMgr::runBackwardRight() {

	GPIO_ResetBits(GPIOE, GPIO_Pin_13);
	GPIO_SetBits(GPIOE, GPIO_Pin_15);
}

void BinaryMotorMgr::stopLeftDoor() {
	GPIO_ResetBits(GPIOE, GPIO_Pin_9);
	GPIO_ResetBits(GPIOE, GPIO_Pin_11);


}

void BinaryMotorMgr::stopRightDoor() {
	GPIO_ResetBits(GPIOE, GPIO_Pin_13);
	GPIO_ResetBits(GPIOE, GPIO_Pin_15);

}
